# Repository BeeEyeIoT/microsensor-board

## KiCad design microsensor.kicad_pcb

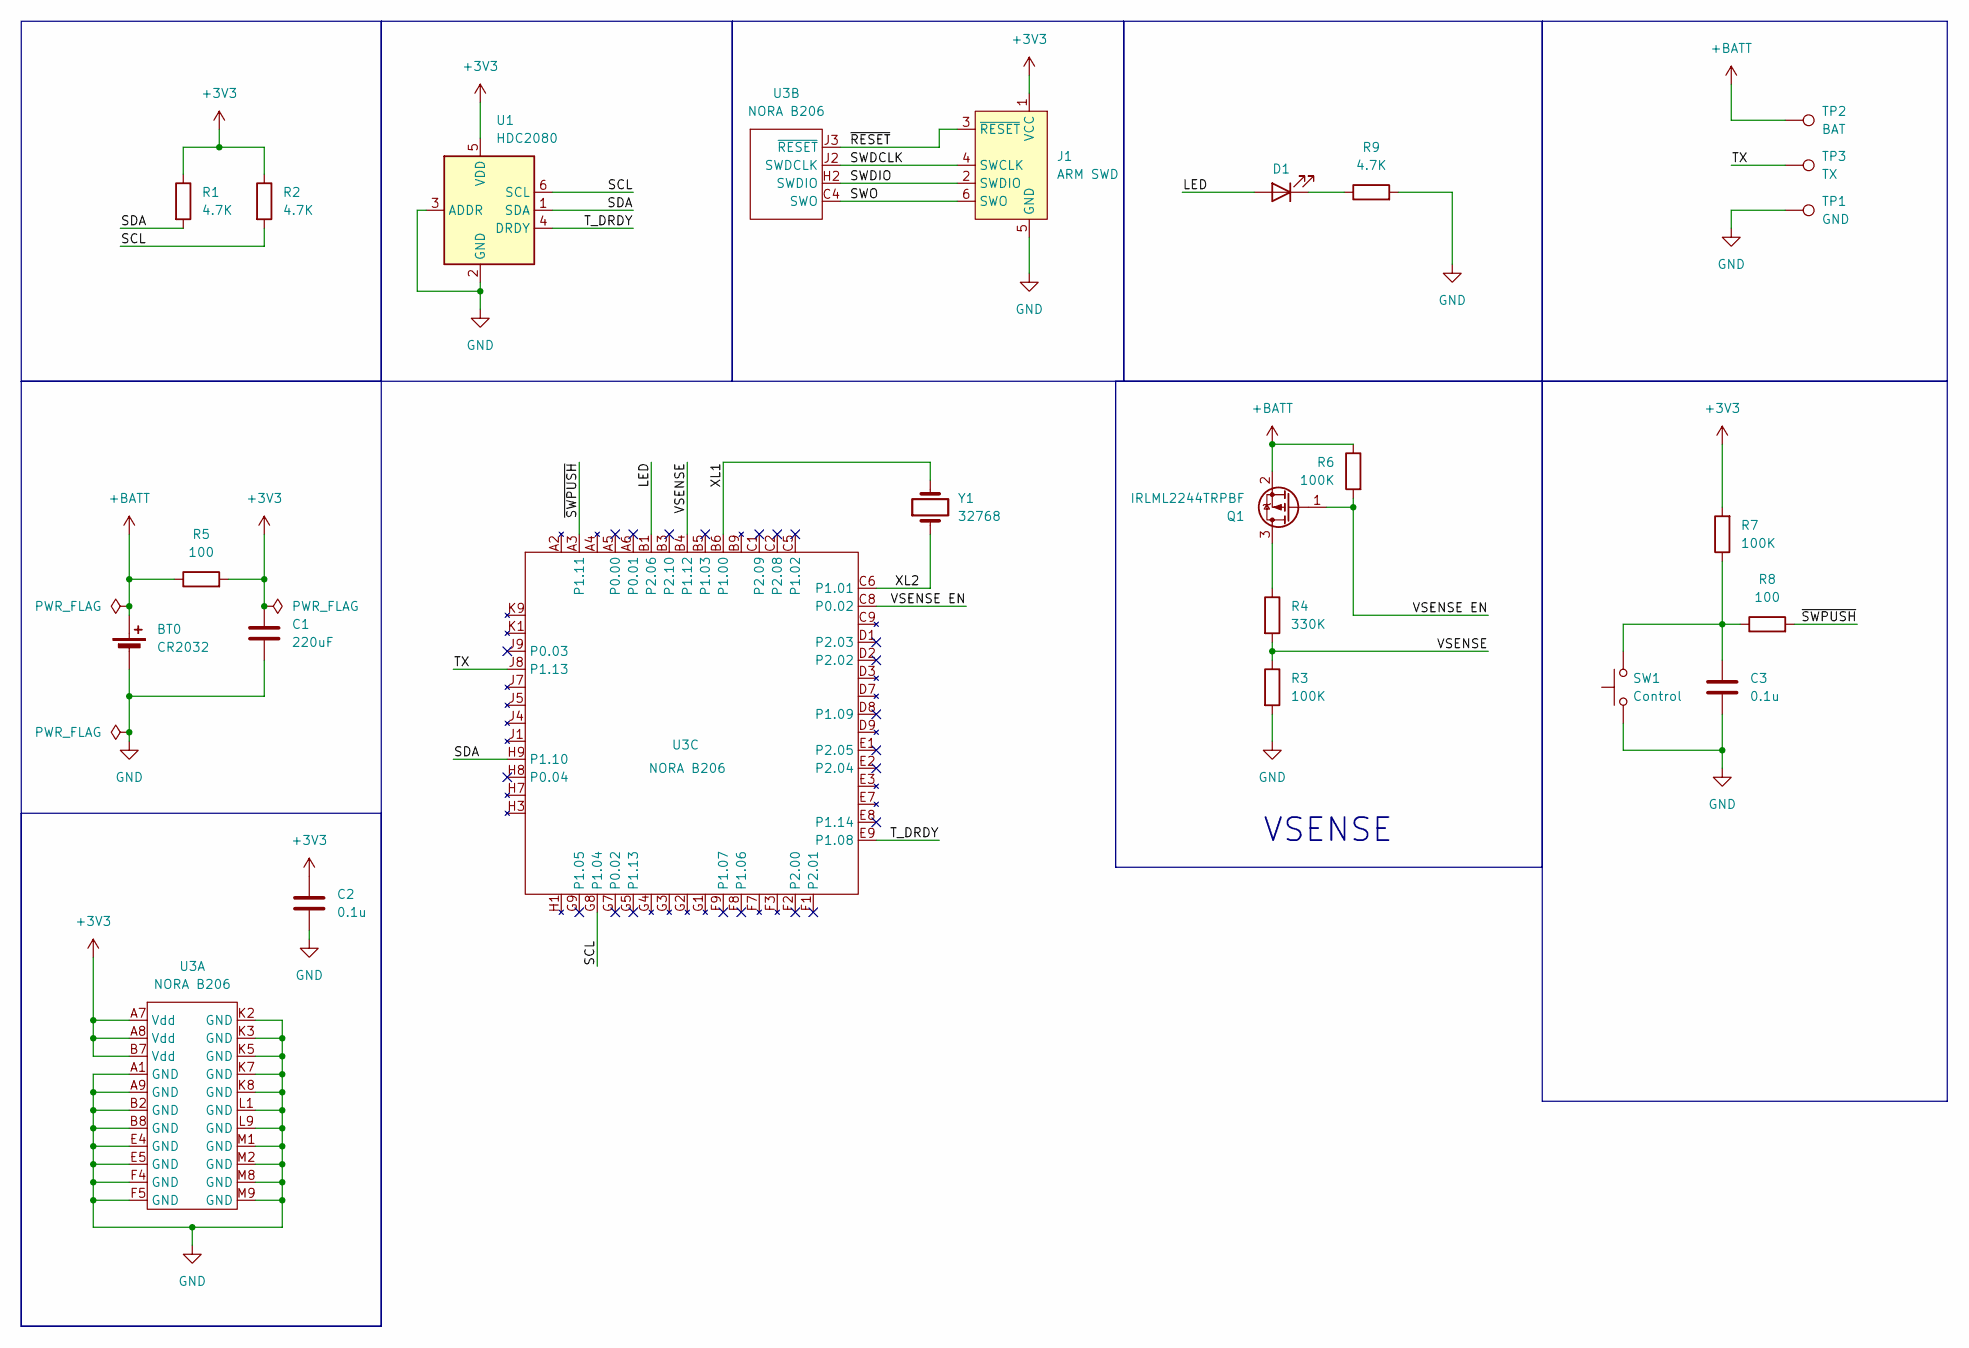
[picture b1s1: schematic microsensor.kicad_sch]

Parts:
BT0: CR2032; Keystone 110 and 112 for CR20xx
C1: 220uF; C_1206_3216Metric
C2, C3: 0.1u; C_0805_2012Metric
D1: LED; LED_1206_3216Metric
J1: ARM SWD; Tag-Connect_TC2030-IDC-NL_2x03_P1.27mm_Vertical
Q1: IRLML2244TRPBF; SOT-23
R1, R2, R9: 4.7K; R_0805_2012Metric
R3, R6, R7: 100K; R_0805_2012Metric
R4: 330K; R_0805_2012Metric
R5, R8: 100; R_0805_2012Metric
SW1: Control; B3U-1000P
TP1: GND; TestPoint_Pad_1.5x1.5mm
TP2: BAT; TestPoint_Pad_1.5x1.5mm
TP3: TX; TestPoint_Pad_1.5x1.5mm
U1: HDC2080; Texas_S-PWSON-N6-HDC2080
U3: NORA B206; NORA-B2x6
Y1: 32768; Crystal_SMD_2012-2Pin_2.0x1.2mm

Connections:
+3V3: C1.1, C2.1, J1.1 (VCC), R1.1, R2.1, R5.2, R7.2, U1.5 (VDD), U3.A7 (Vdd), U3.A8 (Vdd), U3.B7 (Vdd)
+BATT: BT0.1 (+), Q1.2 (S), R5.1, R6.1, TP2.1 (1_1)
/LED: D1.2 (A), U3.B1 (P2.06)
/SCL: R2.2, U1.6 (SCL), U3.G8 (P1.04)
/SDA: R1.2, U1.1 (SDA), U3.H9 (P1.10)
/SWDCLK: J1.4 (SWCLK), U3.J2 (SWDCLK)
/SWDIO: J1.2 (SWDIO), U3.H2 (SWDIO)
/SWO: J1.6 (SWO), U3.C4 (SWO)
/TX: TP3.1 (1_1), U3.J8 (P1.13)
/T_DRDY: U1.4 (DRDY), U3.E9 (P1.08)
/VSENSE: R3.1, R4.2, U3.B4 (P1.12)
/VSENSE EN: Q1.1 (G), R6.2, U3.C8 (P0.02)
/XL1: U3.B6 (P1.00), Y1.2
/XL2: U3.C6 (P1.01), Y1.1
/~RESET: J1.3 (~RESET), U3.J3 (~RESET)
/~SWPUSH: R8.2, U3.A3 (P1.11)
GND: BT0.2 (-), C1.2, C2.2, C3.2, J1.5 (GND), R3.2, R9.2, SW1.1, TP1.1 (1_1), U1.2 (GND), U1.3 (ADDR), U3.A1 (GND), U3.A9 (GND), U3.B2 (GND), U3.B8 (GND), U3.E4 (GND), U3.E5 (GND), U3.F4 (GND), U3.F5 (GND), U3.K2 (GND), U3.K3 (GND), U3.K5 (GND), U3.K7 (GND), U3.K8 (GND), U3.L1 (GND), U3.L9 (GND), U3.M1 (GND), U3.M2 (GND), U3.M8 (GND), U3.M9 (GND)
unnamed: C3.1, R7.1, R8.1, SW1.2
unnamed: D1.1 (K), R9.1
unnamed: Q1.3 (D), R4.1

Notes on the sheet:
VSENSE

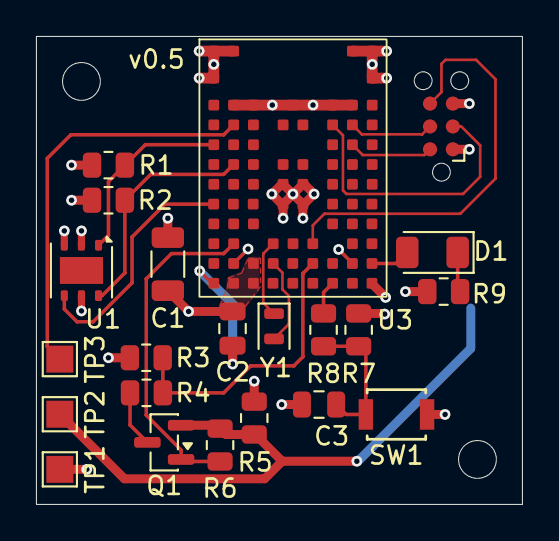
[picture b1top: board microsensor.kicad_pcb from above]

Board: 4 copper layers, 27.0 x 26.0 mm, 25 parts (1 on the bottom side), 20 nets.

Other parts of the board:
MH1, MH2: MountingHole_2.1mm

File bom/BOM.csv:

"Reference","Value","Datasheet","Footprint","Qty","DNP"
"BT0","CR2032","","footprints:Keystone 110 and 112 for CR20xx","1",""
"C1","220uF","","Capacitor_SMD:C_1206_3216Metric","1",""
"C2,C3","0.1u","","Capacitor_SMD:C_0805_2012Metric","2",""
"D1","LED","","LED_SMD:LED_1206_3216Metric","1",""
"Q1","IRLML2244TRPBF","https://www.infineon.com/dgdl/irlml2244pbf.pdf?fileId=5546d4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","Package_TO_SOT_SMD:SOT-23","1",""
"R1,R2,R9","4.7K","","Resistor_SMD:R_0805_2012Metric","3",""
"R3,R6,R7","100K","","Resistor_SMD:R_0805_2012Metric","3",""
"R4","330K","","Resistor_SMD:R_0805_2012Metric","1",""
"R5,R8","100","","Resistor_SMD:R_0805_2012Metric","2",""
"SW1","Control","","footprints:B3U-1000P","1",""
"U1","HDC2080","http://www.ti.com/lit/ds/symlink/hdc2080.pdf","Sensor_Humidity:Texas_S-PWSON-N6-HDC2080","1",""
"U3","NORA B206","","footprints:NORA-B2x6","1",""
"Y1","32768","","Crystal:Crystal_SMD_2012-2Pin_2.0x1.2mm","1",""
